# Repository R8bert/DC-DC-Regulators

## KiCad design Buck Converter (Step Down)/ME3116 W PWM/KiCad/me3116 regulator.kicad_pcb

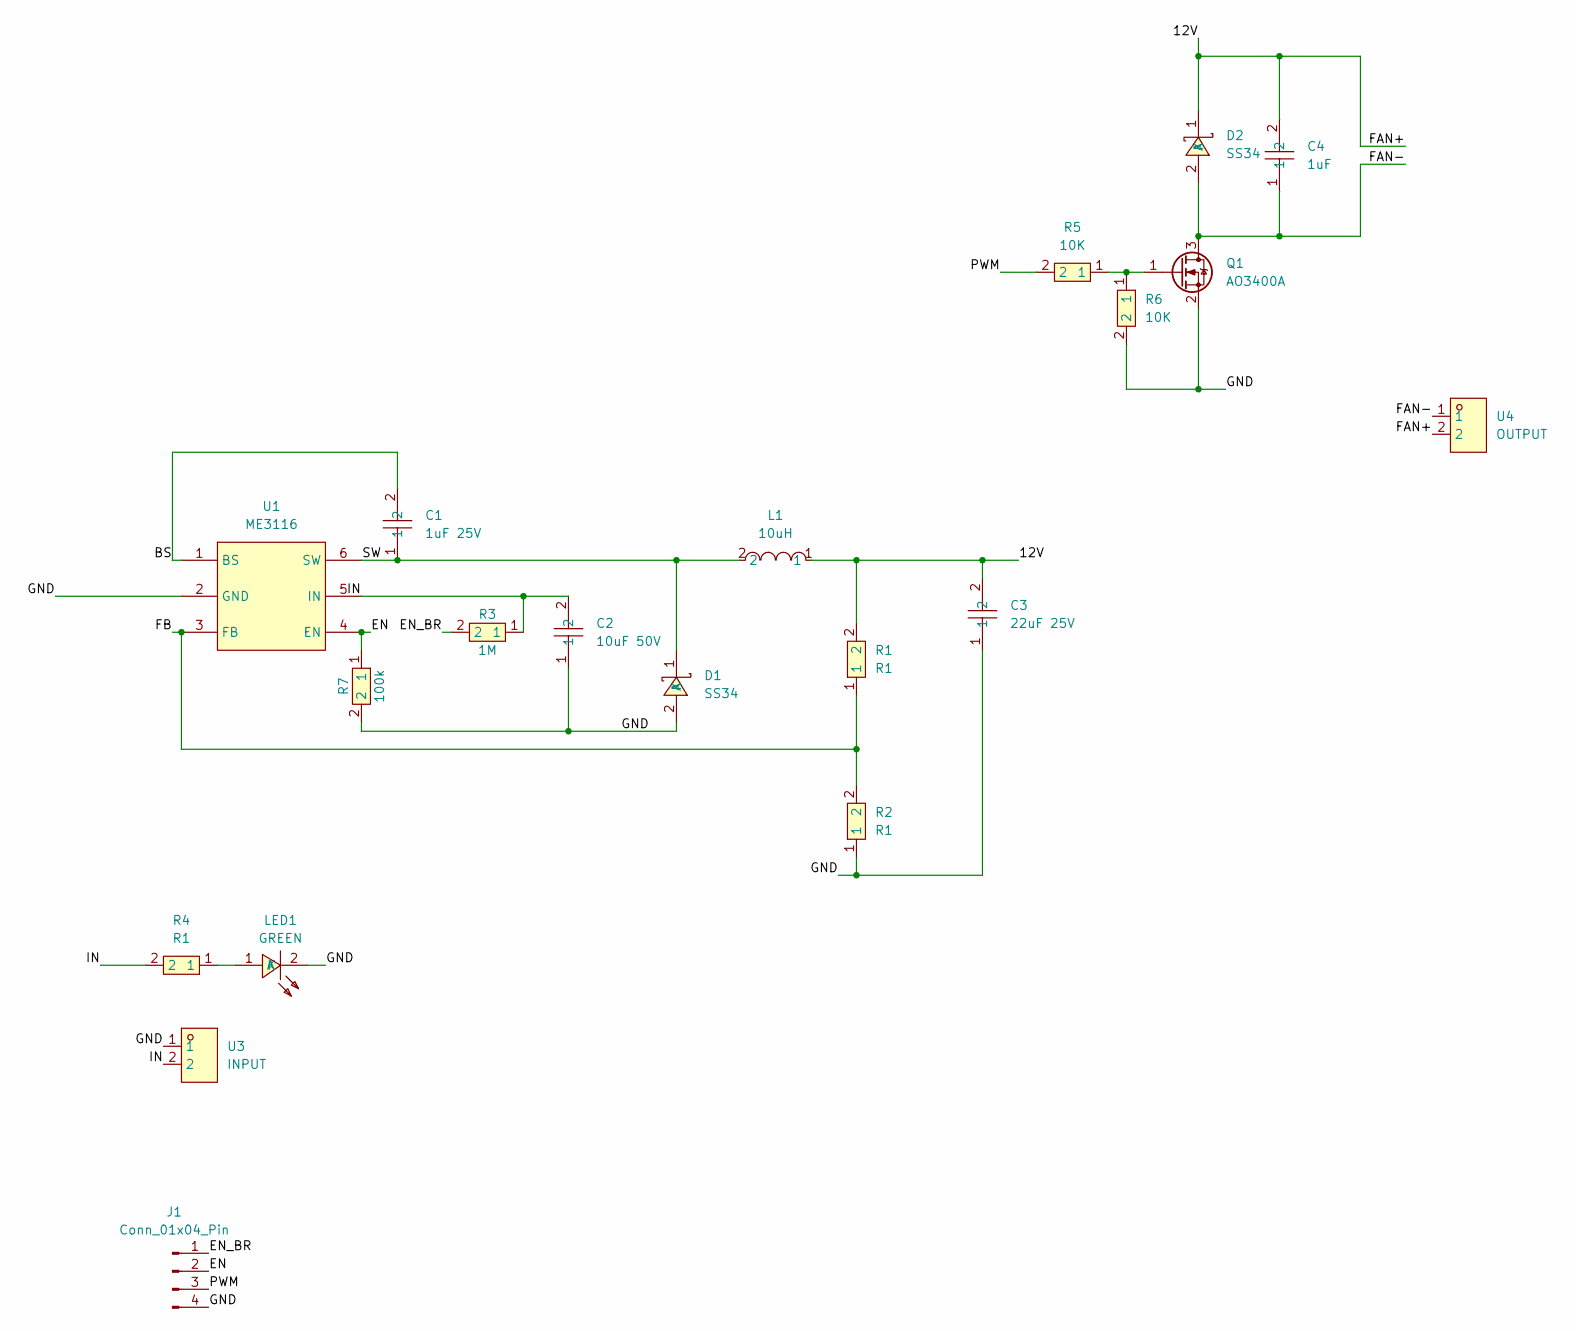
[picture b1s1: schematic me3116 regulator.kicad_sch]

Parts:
C1: 1uF 25V; C0603; LCSC Part C282519
C2: 10uF 50V; C1210; LCSC Part C2918502
C3: 22uF 25V; C1210; LCSC Part C2918502
C4: 1uF; C0603; LCSC Part C282519
D1, D2: SS34; SMA_L4.3-W2.6-LS5.2-RD; LCSC Part C8678
J1: Conn_01x04_Pin; PinSocket_1x04_P2.54mm_Vertical
L1: 10uH; IND-SMD_L7.0-W6.6_0630CDMCCDS; LCSC Part C2961890
LED1: GREEN; LED0603-R-RD; LCSC Part C205450
Q1: AO3400A; SOT-23
R1, R2, R4: R1; R0603; LCSC Part C2918515
R3: 1M; R0603; LCSC Part C2918515
R5, R6: 10K; R0603; LCSC Part C2918515
R7: 100k; R0603; LCSC Part C2918515
U1: ME3116; SOT-23-6_L2.9-W1.6-P0.95-LS2.8-BL; LCSC Part C97643
U3: INPUT; CONN-TH_P5.00_KF301-5.0-2P; LCSC Part C474881
U4: OUTPUT; CONN-TH_P5.00_KF301-5.0-2P; LCSC Part C474881

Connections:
/12V: C3.2, C4.2, D2.1 (K), L1.1, R1.2, U4.2
/BS: C1.2, U1.1 (BS)
/EN: J1.2, R7.1, U1.4 (EN)
/EN_BR: J1.1, R3.2
/FAN-: C4.1, D2.2 (A), Q1.3 (D), U4.1
/FB: R1.1, R2.2, U1.3 (FB)
/GND: C2.1, C3.1, D1.2 (A), J1.4, LED1.2 (K), Q1.2 (S), R2.1, R6.2, R7.2, U1.2 (GND), U3.1
/IN: C2.2, R3.1, R4.2, U1.5 (IN), U3.2
/PWM: J1.3, R5.2
/SW: C1.1, D1.1 (K), L1.2, U1.6 (SW)
unnamed: LED1.1 (A), R4.1
unnamed: Q1.1 (G), R5.1, R6.1

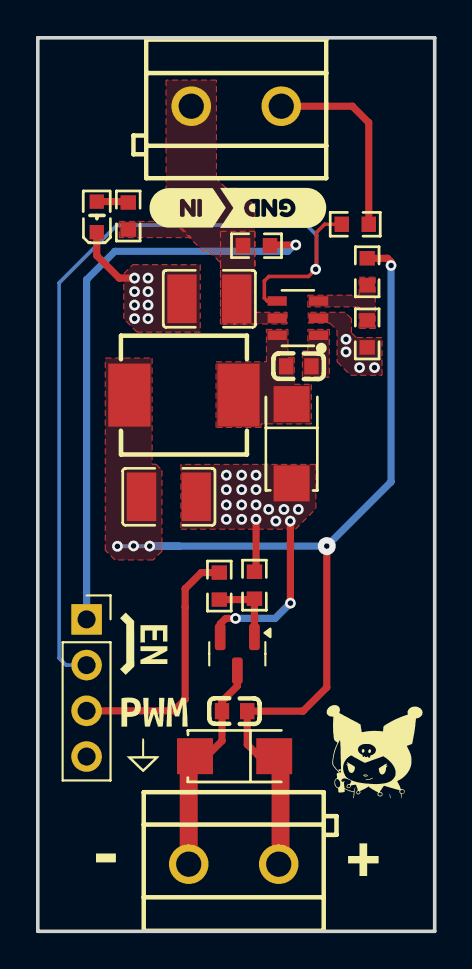
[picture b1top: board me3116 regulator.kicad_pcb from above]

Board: 2 copper layers, 22.0 x 49.6 mm, 26 parts (0 on the bottom side), 12 nets.

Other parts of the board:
kibuzzard-67E9F36D: G***; kibuzzard-67E9F36D
kibuzzard-67E9F317: G***; kibuzzard-67E9F317
kibuzzard-67F7E74D: G***; kibuzzard-67F7E74D
kibuzzard-67F7E75E: G***; kibuzzard-67F7E75E
kibuzzard-68139A75: G***; kibuzzard-68139A75
kibuzzard-68139A87: G***; kibuzzard-68139A87

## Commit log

2025-11-05 ME3116+
2026-01-14 Update readme.md for ME3116 Step-Down Converter
